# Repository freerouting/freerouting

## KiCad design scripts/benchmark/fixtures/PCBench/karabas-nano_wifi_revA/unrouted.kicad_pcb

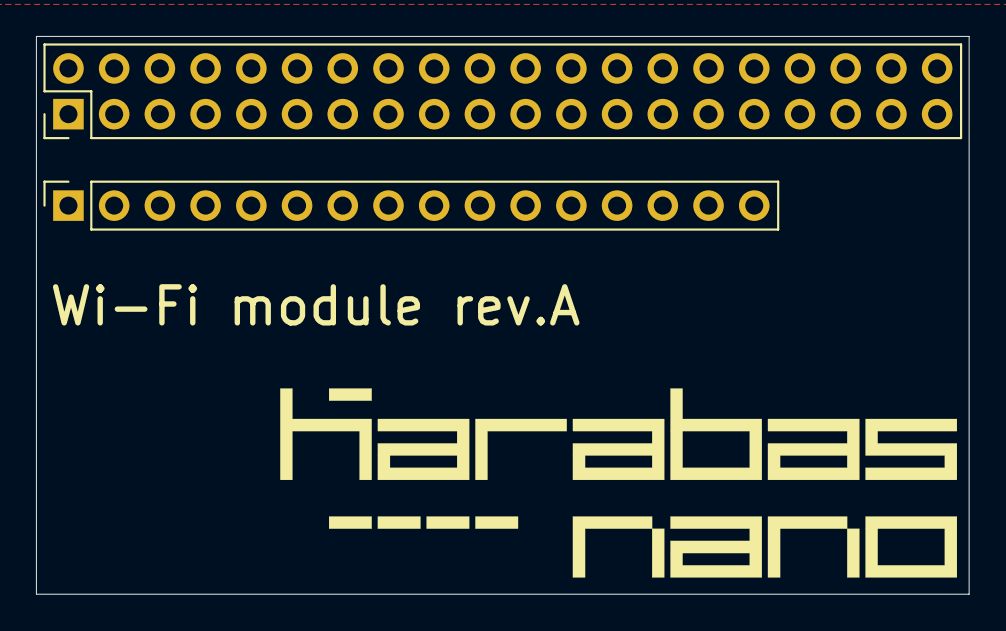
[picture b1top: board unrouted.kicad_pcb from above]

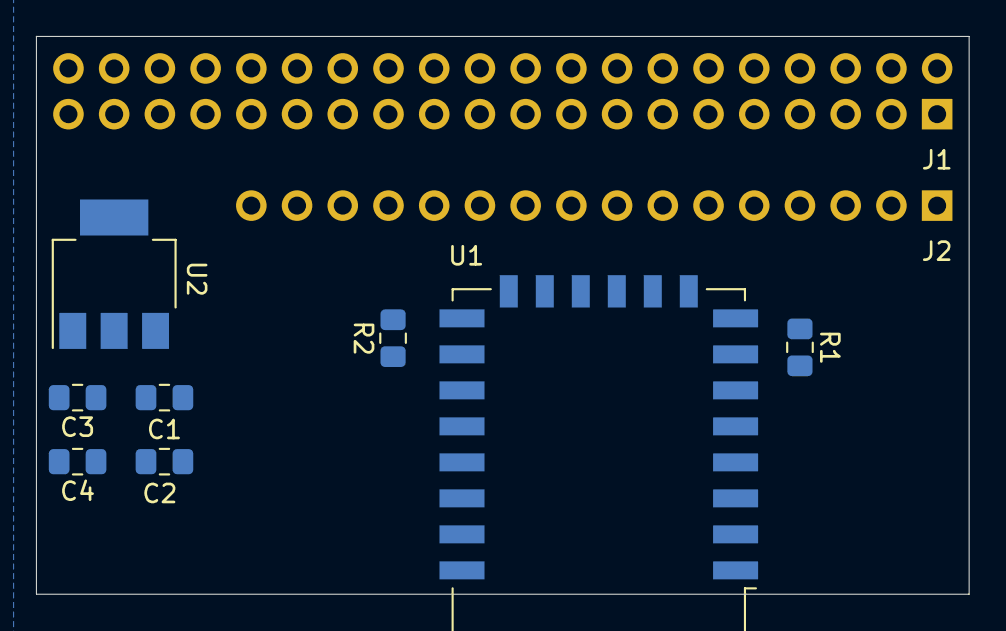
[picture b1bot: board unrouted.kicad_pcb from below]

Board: 2 copper layers, 51.8 x 31.0 mm, 10 parts (8 on the bottom side), 9 nets, no tracks yet.

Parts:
C1, C4: 100nF; C_0805_2012Metric_Pad1.15x1.40mm_HandSolder
C2, C3: 1uF; C_0805_2012Metric_Pad1.15x1.40mm_HandSolder
J1: ZX BUS; PinHeader_2x20_P2.54mm_Vertical
J2: ZX BUS; PinSocket_1x16_P2.54mm_Vertical
R1, R2: 10k; R_0805_2012Metric_Pad1.15x1.40mm_HandSolder
U1: ESP-12E
U2: AMS1117-3.3; SOT-223-3_TabPin2

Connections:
+3V3: C3.1, C4.1, R1.1, U1.8, U2.2
GND: C1.2, C2.2, C3.2, C4.2, J1.40, R2.2, U1.15, U2.1
unnamed: R1.2, U1.3
unnamed: R2.1, U1.16
UART_CTS: J1.4, U1.7
UART_RX: J2.15, U1.22
UART_TX: J1.6, U1.21
VCC: C1.1, C2.1, J1.39, U2.3
~RESET: J2.16, U1.1

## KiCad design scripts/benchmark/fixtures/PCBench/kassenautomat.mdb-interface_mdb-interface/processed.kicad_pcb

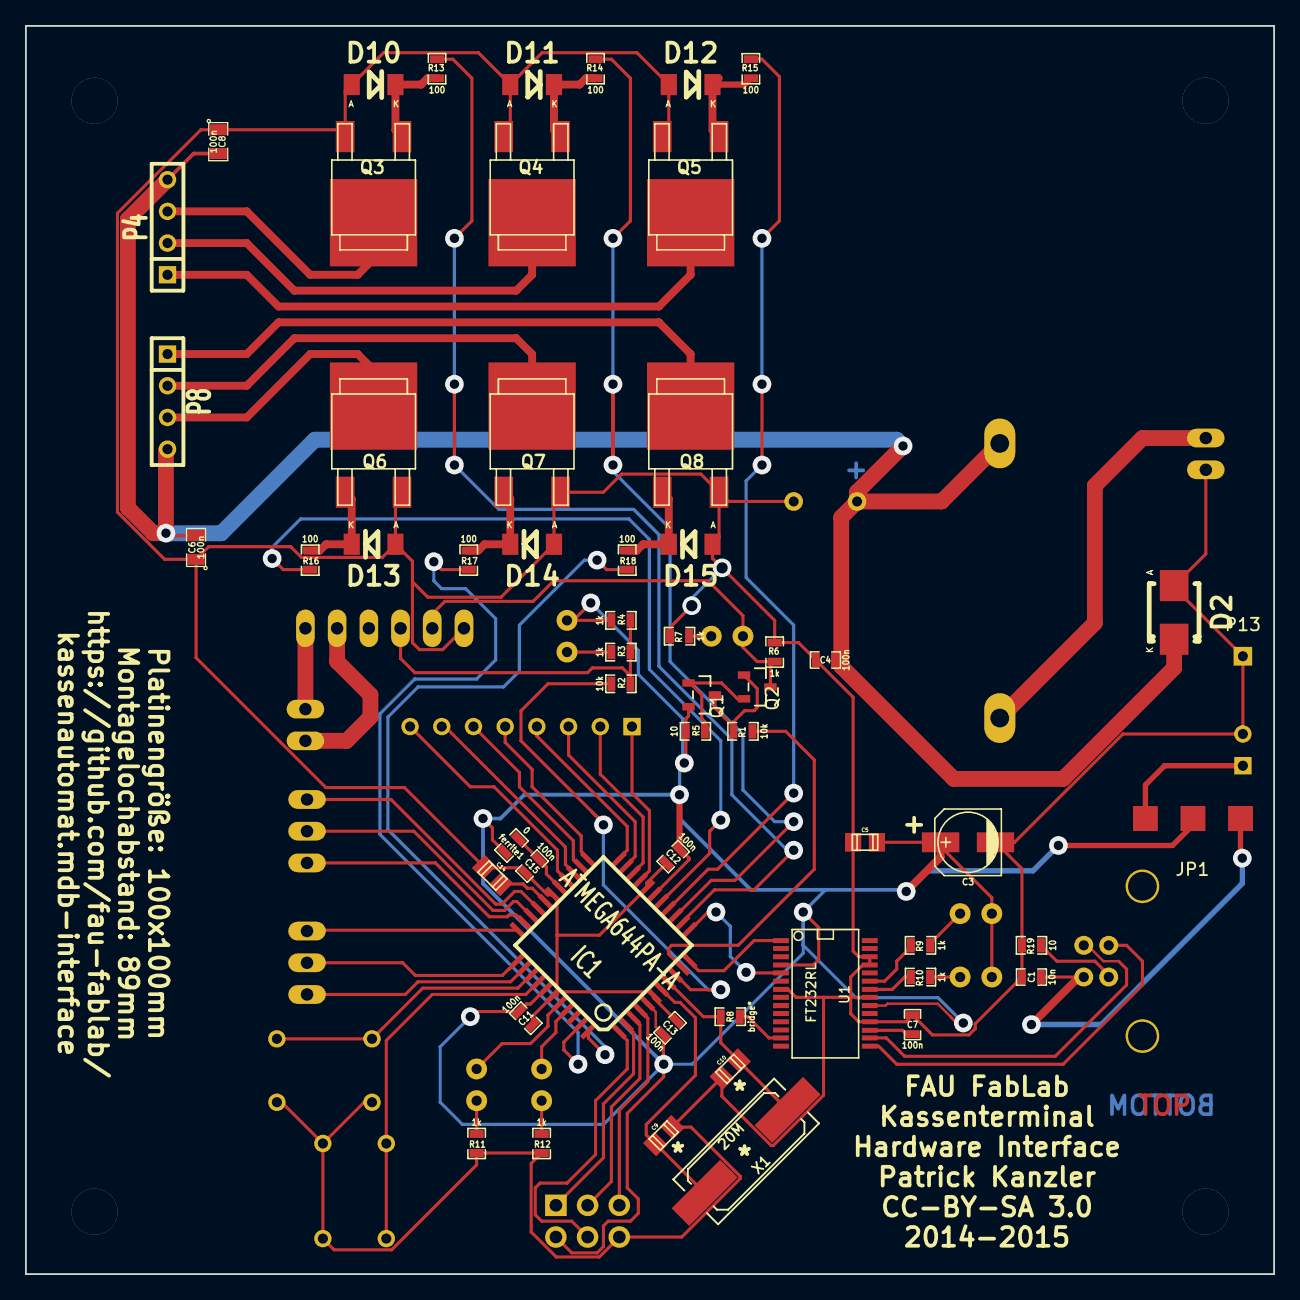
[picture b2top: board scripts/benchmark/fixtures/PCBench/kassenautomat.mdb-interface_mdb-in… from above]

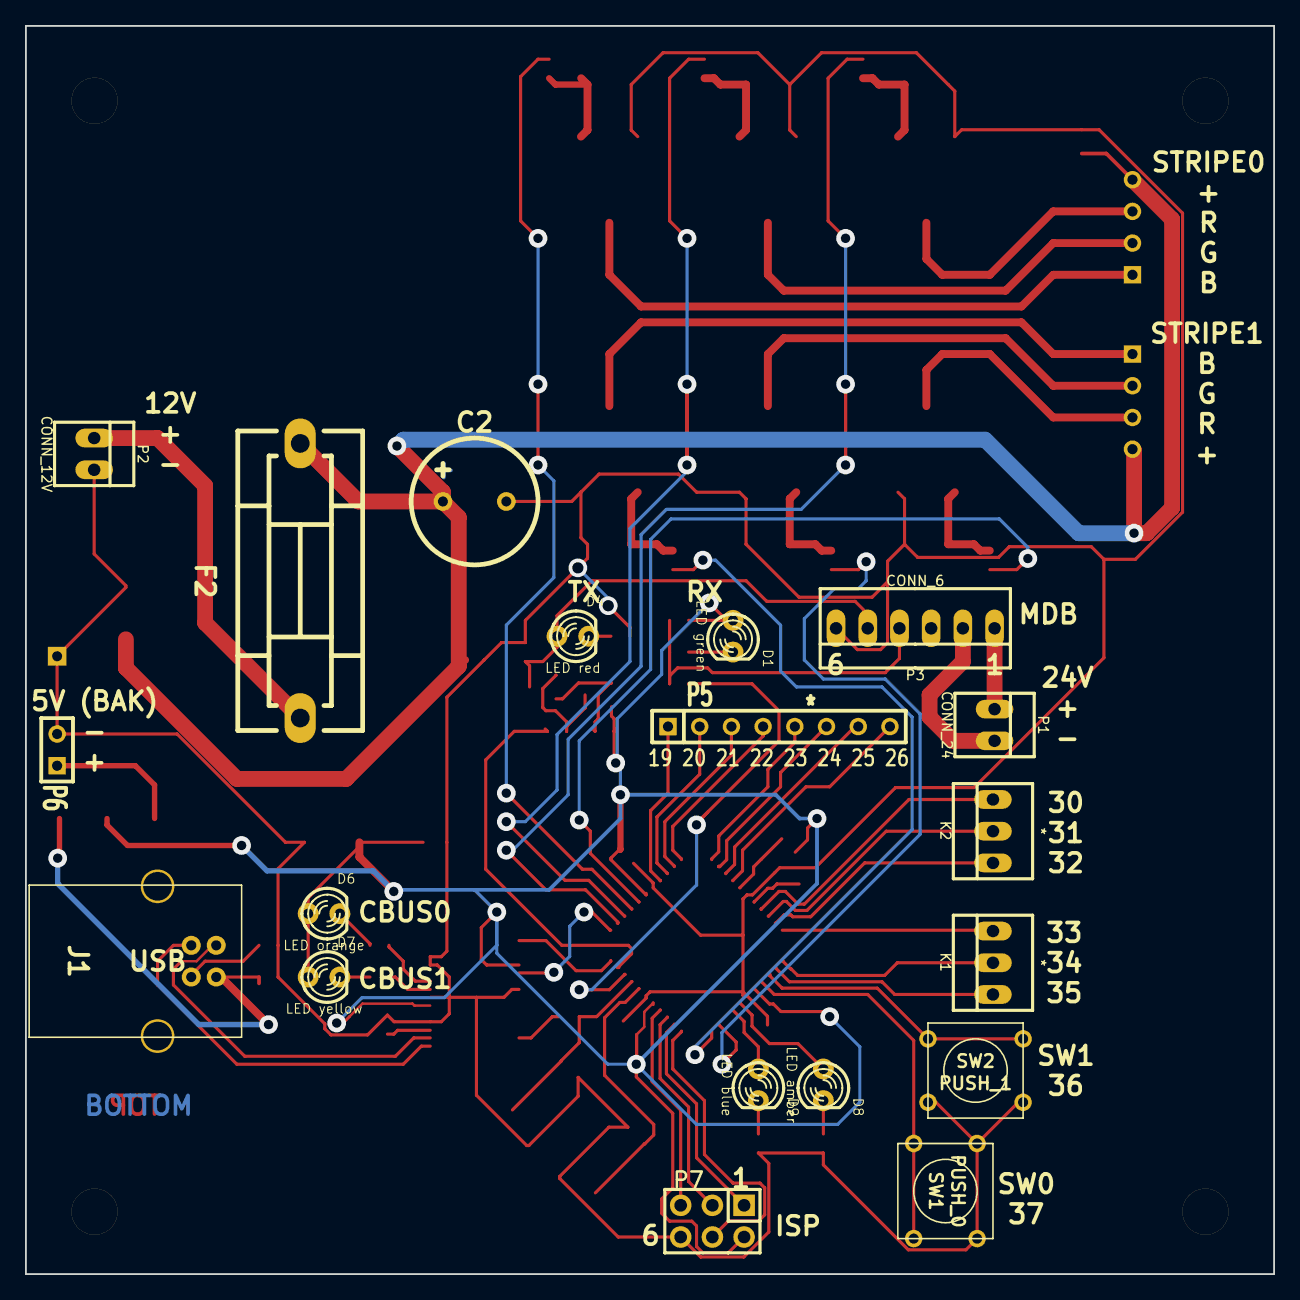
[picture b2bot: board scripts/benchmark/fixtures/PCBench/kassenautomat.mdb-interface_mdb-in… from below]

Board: 2 copper layers, 100.0 x 100.0 mm, 79 parts (19 on the bottom side), 73 nets.

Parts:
C1: 10n; SM0603_Capa
C2: 470u; Elko_vert_DM10_RM5_CopperClear
C3: * 47u 6,3V; c_elec_5x5.8
C4, C7, C11, C12, C13, C15: 100n; SM0603_Capa
C5, C14: 1u; c_0805
C6, C8: 100n; SM0805
C9, C10: 22p; c_0805
D1: LED green; LED-3MM
D2: SM6T15A; Diode-SMB_Standard
D4: LED red; LED-3MM
D6: LED orange; LED-3MM
D7: LED yellow; LED-3MM
D8: LED amber; LED-3MM
D9: LED blue; LED-3MM
D10, D11, D12, D13, D14, D15: ZD5.1; Diode-MiniMELF_Standard
F2: FUSE; Fuseholder5x20_horiz_SemiClosed_Casing10x25mm
IC1: ATMEGA644PA-A; TQFP44
J1: USB; USB_B
JP1: JUMPER3; NetTie-II_SMD
K1, K2: *; PINHEAD1-3
P1: CONN_24; PINHEAD1-2
P2: CONN_12V; PINHEAD1-2
P3: CONN_6; PINHEAD1-6
P4, P8: CONN_4; SIL-4
P5: *; SIL-8
P6: *; SIL-2
P7: CONN_6; Pin_Header_Straight_2x03
P9, P10, P11, P12: CONN_1; MountingHole_3-7mm
P13: CONN_01X01; Measurement_Point_Square-TH_Small
Q1, Q2: BCW67; sot23
Q3, Q4, Q5, Q6, Q7, Q8: MOSFET_N; sot428
R1, R2: 10k; SM0603_Resistor
R3, R4, R6, R7, R9, R10, R11, R12: 1k; SM0603_Resistor
R5, R19: 10; SM0603_Resistor
R8: bridge*; SM0603_Resistor
R13, R14, R15, R16, R17, R18: 100; SM0603_Resistor
SW1: PUSH_0; SW_PUSH_SMALL
SW2: PUSH_1; SW_PUSH_SMALL
U1: FT232RL; SSOP28
X1: 20M; Q_49U3HMS
ferrite1: 0; SM0603_Resistor

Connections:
+5V: C3.1, C5.1, C11.1, C12.1, C13.1, D1.1, D6.1, D7.1, IC1.5, IC1.17, IC1.38, JP1.2, P7.2, Q1.2, R4.1, R5.1, U1.4, U1.20, ferrite1.2
+12V: C2.1, C4.1, C6.2, C8.2, D2.2, F2.2, P4.4, P8.4
/12MHz: R8.1, U1.13
/AVR_to_PC: IC1.12, U1.5
/BusRX: IC1.9, R2.1
/BusTX: IC1.10, R1.1
/MDB_MR: P3.4, R2.2, R3.2, R4.2
/MDB_MT: D4.1, P3.5, Q2.3, R6.1
/MISO: IC1.2, P7.1
/MOSI: IC1.1, P7.4
/PC_to_AVR: IC1.11, U1.1
/PWM0_BLUE: P4.1, Q5.D
/PWM0_GREEN: P4.2, Q4.D
/PWM0_RED: P4.3, Q3.D
/PWM1_BLUE: P8.1, Q8.D
/PWM1_GREEN: P8.2, Q7.D
/PWM1_RED: P8.3, Q6.D
/PWM_0: IC1.13, R13.2
/PWM_1: IC1.14, R14.2
/PWM_2: IC1.15, R15.2
/PWM_3: IC1.16, R16.2
/PWM_4: IC1.43, R17.2
/PWM_5: IC1.44, R18.2
/RESET: IC1.4, P7.5
/SCK: IC1.3, P7.3
/VBAK: JP1.1, P6.1
/VUSB: C1.1, J1.1, JP1.3
GND: C1.2, C2.2, C3.2, C4.2, C5.2, C6.1, C7.2, C8.1, C9.1, C10.2, C11.2, C12.2, C13.2, C14.2, C15.2, D2.1, D10.1, D11.1, D12.1, D13.1, D14.1, D15.1, IC1.6, IC1.18, IC1.28, IC1.39, P2.2, P3.6, P6.2, P7.6, P13.1, Q3.S, Q4.S, Q5.S, Q6.S, Q7.S, Q8.S, R6.2, R7.2, R11.2, R12.2, R19.2, SW1.2, SW2.2, U1.7, U1.18, U1.21, U1.25, U1.26
unnamed: C7.1, U1.17
unnamed: C9.2, IC1.7, X1.2
unnamed: C10.1, IC1.8, R8.2, X1.1
unnamed: C14.1, IC1.29
unnamed: C15.1, IC1.27, ferrite1.1
unnamed: D1.2, R3.1
unnamed: D4.2, R7.1
unnamed: D6.2, R9.1
unnamed: D7.2, R10.1
unnamed: D8.1, IC1.40
unnamed: D8.2, R11.1
unnamed: D9.1, IC1.41
unnamed: D9.2, R12.1
unnamed: D10.2, Q3.G, R13.1
unnamed: D11.2, Q4.G, R14.1
unnamed: D12.2, Q5.G, R15.1
unnamed: D13.2, Q6.G, R16.1
unnamed: D14.2, Q7.G, R17.1
unnamed: D15.2, Q8.G, R18.1
unnamed: F2.1, P2.1
unnamed: IC1.19, P5.1
unnamed: IC1.20, P5.2
unnamed: IC1.21, P5.3
unnamed: IC1.22, P5.4
unnamed: IC1.23, P5.5
unnamed: IC1.24, P5.6
unnamed: IC1.25, P5.7
unnamed: IC1.26, P5.8
unnamed: IC1.30, K2.3
unnamed: IC1.31, K2.2
unnamed: IC1.32, K2.1
unnamed: IC1.33, K1.3
unnamed: IC1.34, K1.2
unnamed: IC1.35, K1.1
unnamed: IC1.36, SW2.1
unnamed: IC1.37, SW1.1
unnamed: J1.2, U1.16
unnamed: J1.3, U1.15
unnamed: J1.4, R19.1
unnamed: P1.1, P3.1
unnamed: P1.2, P3.2
unnamed: Q1.1, Q2.2, R5.2
unnamed: Q1.3, Q2.1, R1.2
unnamed: R9.2, U1.23
unnamed: R10.2, U1.22

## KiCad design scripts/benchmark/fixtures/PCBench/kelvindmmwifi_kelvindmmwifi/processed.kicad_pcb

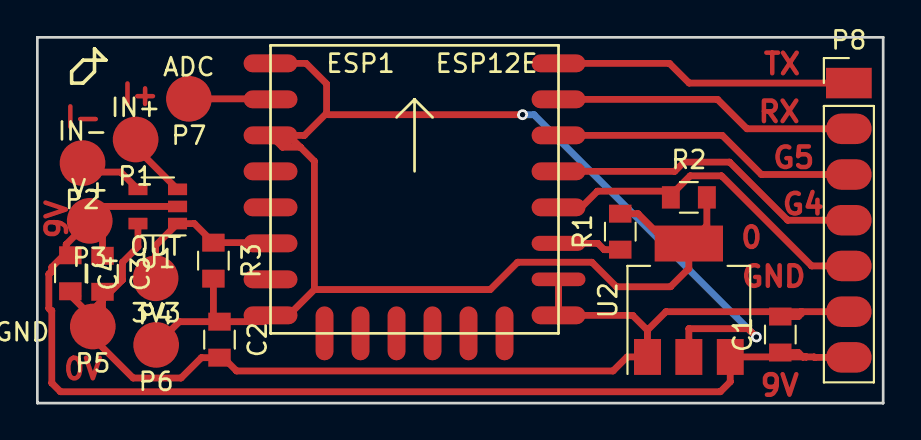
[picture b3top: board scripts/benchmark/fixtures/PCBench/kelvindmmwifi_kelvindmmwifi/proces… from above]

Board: 2 copper layers, 47.0 x 20.3 mm, 18 parts (0 on the bottom side), 13 nets.

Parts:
C1, C2: 10u; C_0805
C3, C4: 0.1; C_0805
ESP1: ESP12E
P1: IN+; SMTPIN.1
P2: IN-; SMTPIN.1
P3: V+; SMTPIN.1
P4: OUT; SMTPIN.1
P5: GND; SMTPIN.1
P6: 3V3; SMTPIN.1
P7: ADC; SMTPIN.1
P8: PGM_ETC; Pin_Header_Straight_1x07_Pitch2.54mm
R1, R2, R3: 10k; C_0805
U1: COMP-MIC7721; SOT-23-5
U2: AP1117; SOT-223

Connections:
+3V3: C2.1, ESP1.1, ESP1.3, ESP1.8, P6.1, R1.2, R2.2, R3.2, U2.2, U2.4
+5V: C1.1, C3.1, C4.1, P3.1, P8.7, U1.2, U2.3
GND: C1.2, C2.2, C3.2, C4.2, ESP1.15, ESP1.16, P5.1, P8.6, U1.5, U2.1
unnamed: ESP1.2, P7.1
unnamed: ESP1.6, P4.1, R3.1, U1.1
unnamed: ESP1.17, R1.1
unnamed: ESP1.18, P8.5, R2.1
unnamed: ESP1.19, P8.4
unnamed: ESP1.20, P8.3
unnamed: ESP1.21, P8.2
unnamed: ESP1.22, P8.1
unnamed: P1.1, U1.3
unnamed: P2.1, U1.4

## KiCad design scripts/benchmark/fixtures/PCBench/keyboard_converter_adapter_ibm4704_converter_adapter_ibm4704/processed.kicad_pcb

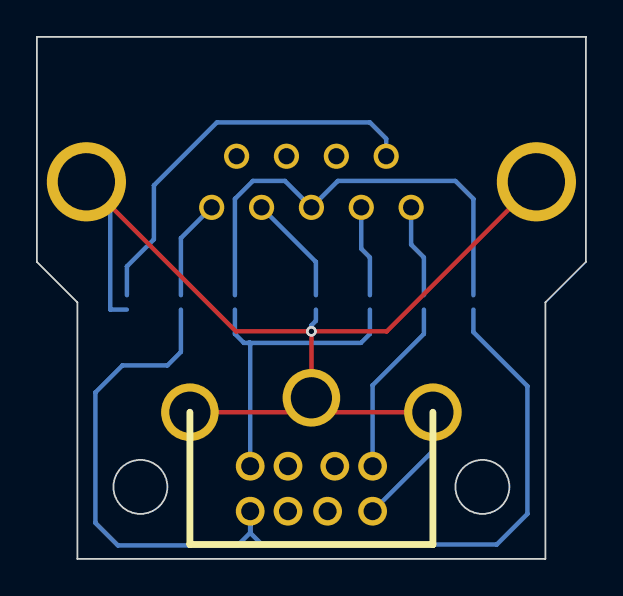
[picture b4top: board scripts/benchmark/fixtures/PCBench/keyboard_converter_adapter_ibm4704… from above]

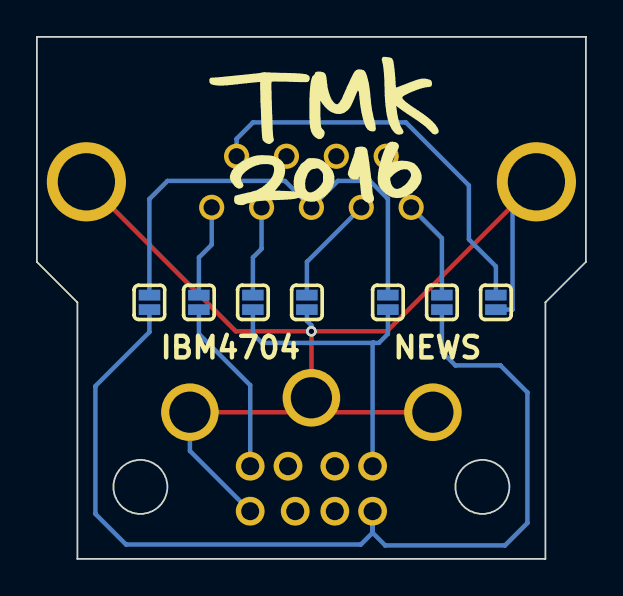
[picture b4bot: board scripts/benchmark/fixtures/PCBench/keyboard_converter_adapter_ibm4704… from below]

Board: 2 copper layers, 30.5 x 29.0 mm, 9 parts (7 on the bottom side), 10 nets.

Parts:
CN1: MINI_DIN_8P_JACK; MINI_DIN_8
P1: CONN_01X10; DSUB9P
SJ1, SJ2, SJ3, SJ4, SJ5, SJ6, SJ7: SOLDER_JUMPER; SOLDER_JUMPER_2

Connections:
/D0: CN1.3, SJ3.1, SJ6.1
/D1: CN1.5, SJ4.1
/DS_1: P1.1, SJ5.2
/DS_2: P1.2, SJ1.2
/DS_3: P1.3, SJ2.2, SJ6.2
/DS_4: P1.4, SJ3.2
/DS_5: P1.5, SJ4.2
/DS_9: P1.9, SJ7.2
/VCC: CN1.6, SJ2.1, SJ5.1
GND: CN1.8, CN1.9, P1.10, SJ1.1, SJ7.1

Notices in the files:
scripts/benchmark/fixtures/PCBench/kassenautomat.mdb-interface_mdb-interface/processed.kicad_pcb:
CC-BY-SA 3.0
